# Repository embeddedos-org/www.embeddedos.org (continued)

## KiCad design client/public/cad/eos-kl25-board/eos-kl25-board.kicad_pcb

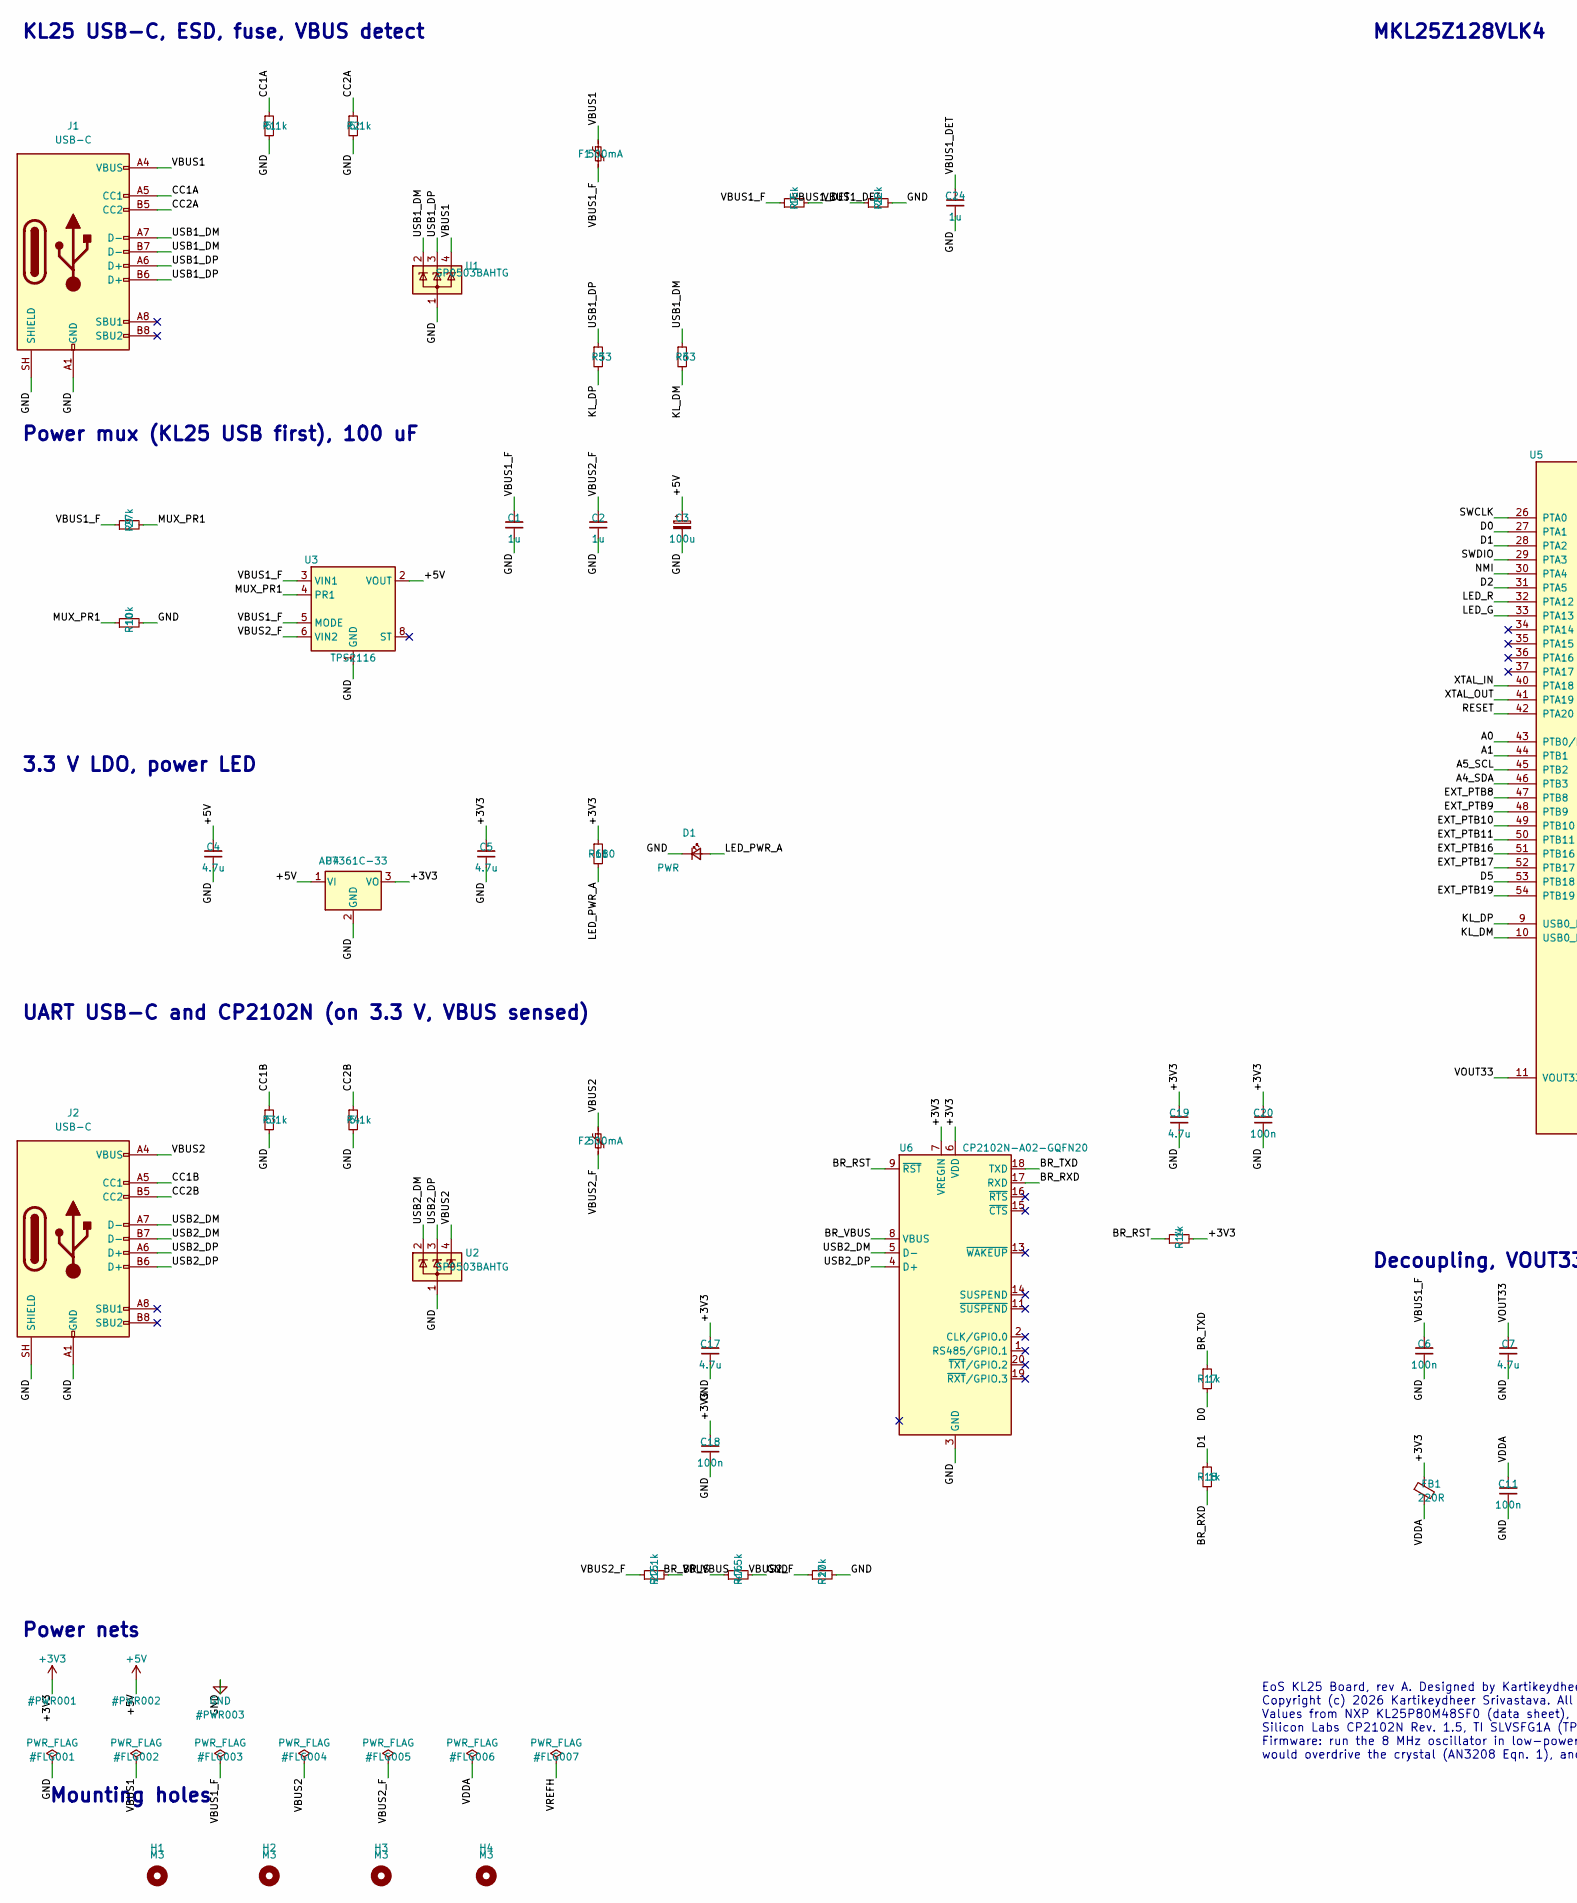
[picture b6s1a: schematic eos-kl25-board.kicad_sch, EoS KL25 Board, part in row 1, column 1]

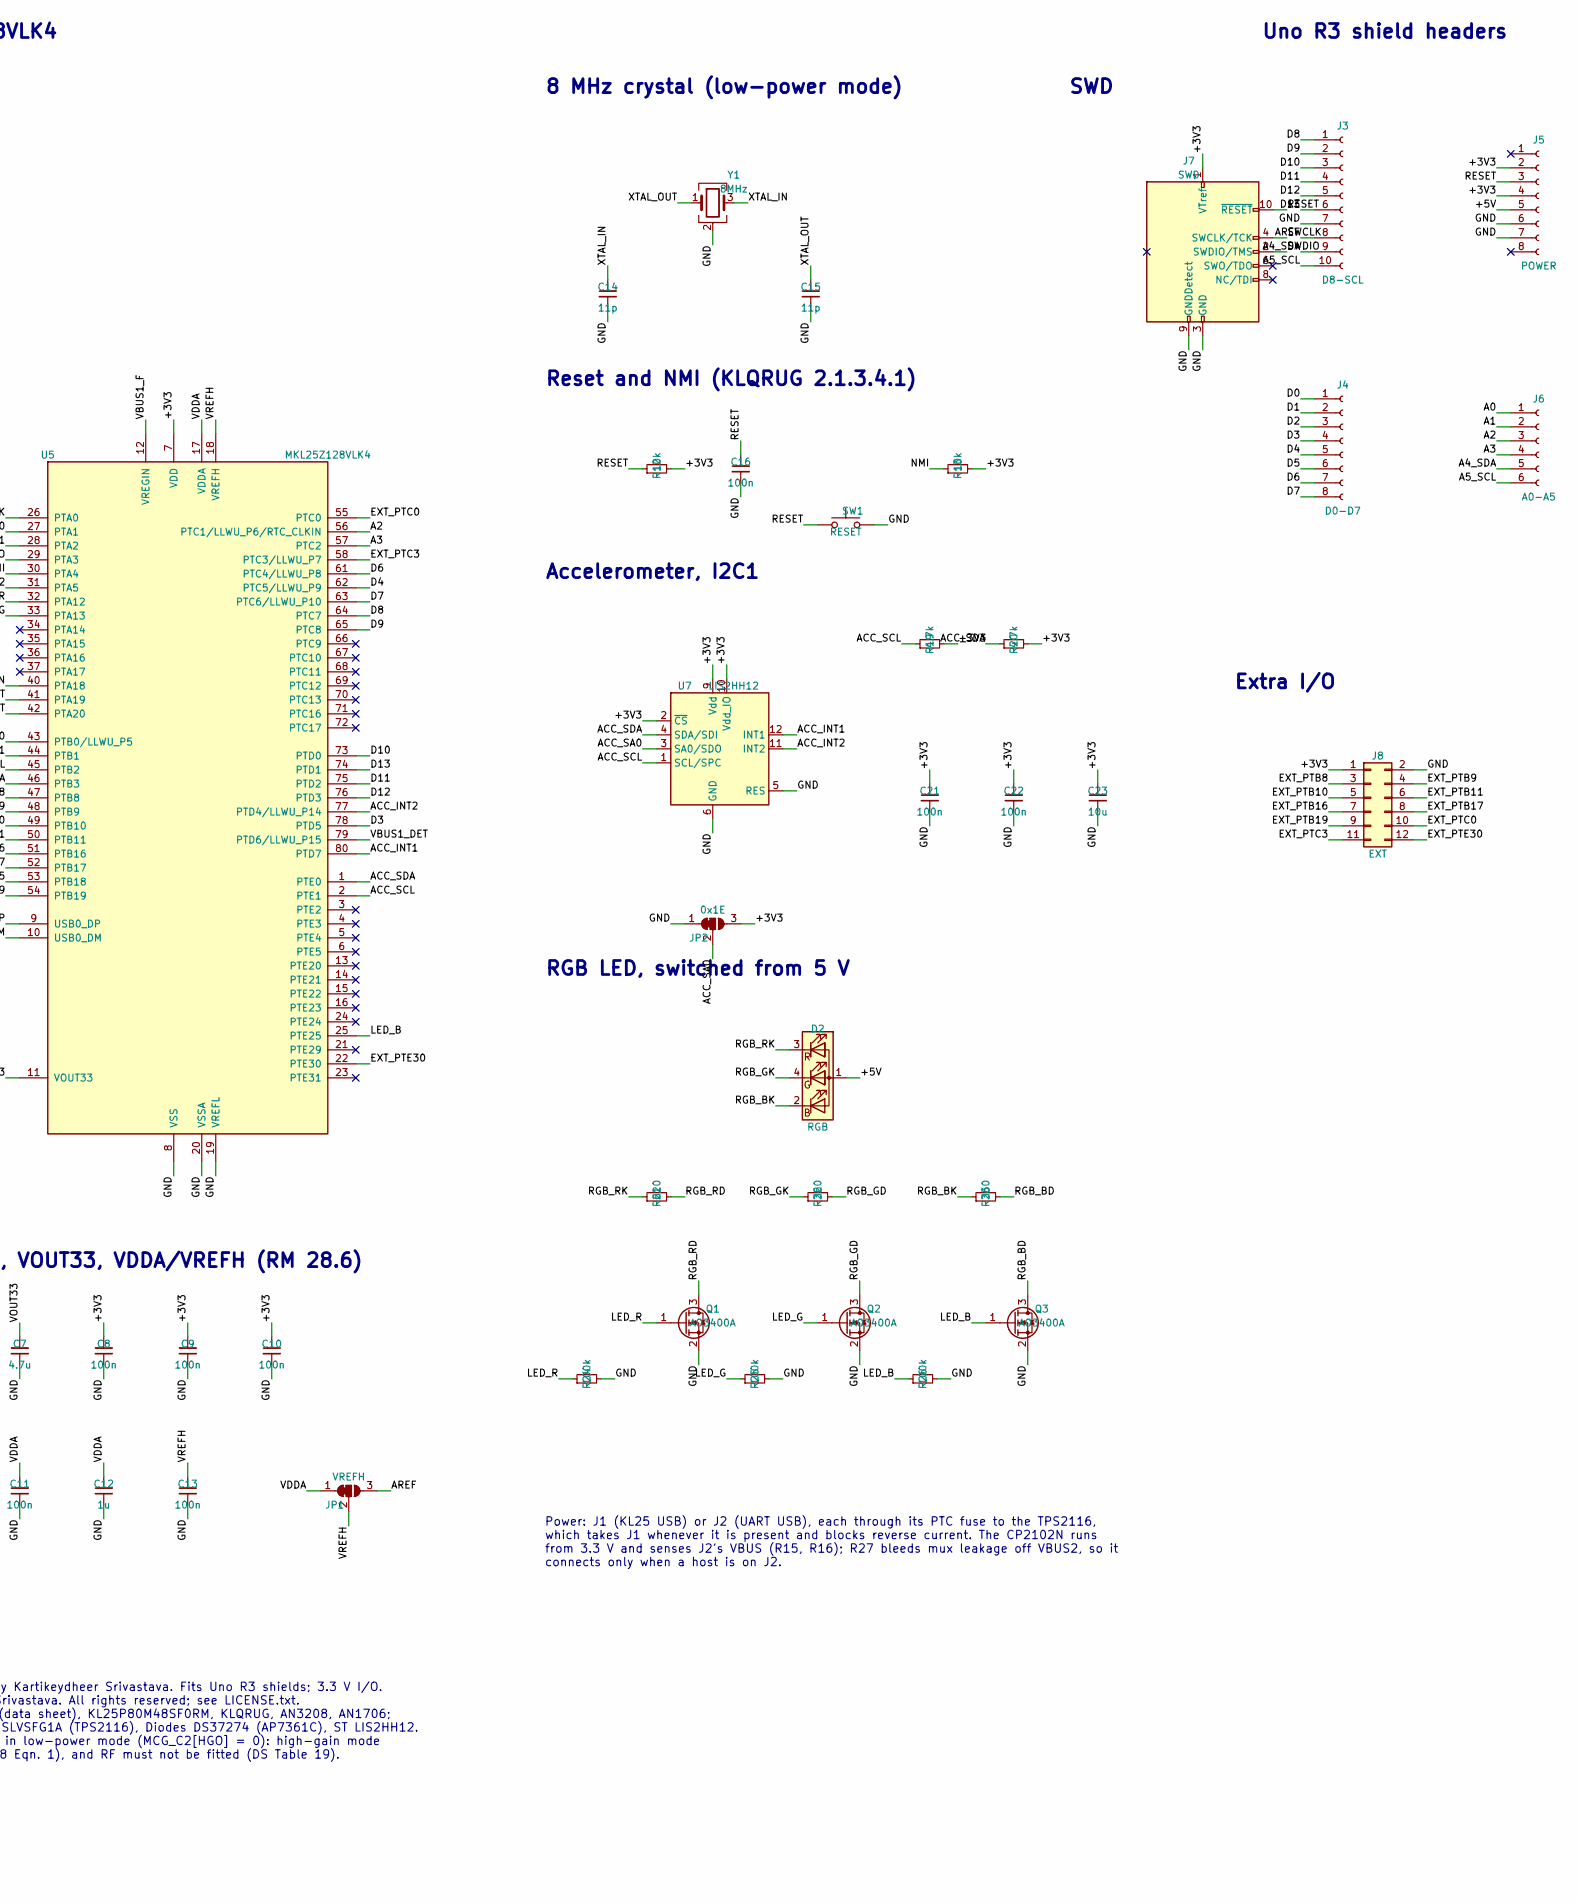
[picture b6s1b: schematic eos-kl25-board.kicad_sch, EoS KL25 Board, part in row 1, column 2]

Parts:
C1, C2, C12, C24: 1u; C_0603_1608Metric; MPN GCM188R71C105KA64D
C3: 100u; CP_Elec_6.3x5.8; MPN EEE-FK1C101P
C4: 4.7u; C_0805_2012Metric; MPN GRM219R61E475KA73D
C5, C7, C17, C19: 4.7u; C_0805_2012Metric; MPN GRM21BR71A475KE51L
C6, C8, C9, C10, C11, C13, C16, C18, C20, C21, C22: 100n; C_0402_1005Metric; MPN GRM155R71C104KA88D
C14, C15: 11p; C_0402_1005Metric; MPN GJM1555C1H110JB01D
C23: 10u; C_0805_2012Metric; MPN GRM21BR61C106KE15L
D1: PWR; LED_0603_1608Metric; MPN APTD1608LCGCK
D2: RGB; LED_RGB_Wuerth-PLCC4_3.2x2.8mm_150141M173100; MPN 150141M173100
F1, F2: 500mA; Fuse_1206_3216Metric; MPN MF-NSMF050/8X-2
FB1: 220R; L_0603_1608Metric; MPN BLM18PG221SN1D
H1, H2, H3, H4: M3; MountingHole_3.2mm_M3_ISO14580
J1, J2: USB-C; USB_C_Receptacle_HRO_TYPE-C-31-M-12; MPN TYPE-C-31-M-12
J3: D8-SCL; PinSocket_1x10_P2.54mm_Vertical; MPN SSW-110-01-T-S
J4: D0-D7; PinSocket_1x08_P2.54mm_Vertical; MPN SSW-108-01-T-S
J5: POWER; PinSocket_1x08_P2.54mm_Vertical; MPN SSW-108-01-T-S
J6: A0-A5; PinSocket_1x06_P2.54mm_Vertical; MPN SSW-106-01-T-S
J7: SWD; PinHeader_2x05_P1.27mm_Vertical_SMD; MPN FTSH-105-01-L-DV-K
J8: EXT; PinHeader_2x06_P2.54mm_Vertical; MPN TSW-106-07-G-D
JP1: VREFH; SolderJumper-3_P1.3mm_Bridged12_RoundedPad1.0x1.5mm
JP2: 0x1E; SolderJumper-3_P1.3mm_Bridged12_RoundedPad1.0x1.5mm
Q1, Q2, Q3: AO3400A; SOT-23; MPN AO3400A
R1, R2, R3, R4: 5.1k; R_0402_1005Metric; MPN RC0402FR-075K1L
R5, R6: 33; R_0402_1005Metric; MPN RC0402FR-0733RL
R7: 15k; R_0402_1005Metric; MPN RC0402FR-0715KL
R8: 22k; R_0402_1005Metric; MPN RC0402FR-0722KL
R9: 27k; R_0402_1005Metric; MPN RC0402FR-0727KL
R10, R12, R13, R27: 10k; R_0402_1005Metric; MPN RC0402FR-0710KL
R11: 680; R_0402_1005Metric; MPN RC0402FR-07680RL
R14, R17, R18: 1k; R_0402_1005Metric; MPN RC0402FR-071KL
R15: 22.1k; R_0402_1005Metric; MPN RC0402FR-0722K1L
R16: 47.5k; R_0402_1005Metric; MPN RC0402FR-0747K5L
R19, R20: 4.7k; R_0402_1005Metric; MPN RC0402FR-074K7L
R21: 620; R_0402_1005Metric; MPN RC0402FR-07620RL
R22, R23: 360; R_0402_1005Metric; MPN RC0402FR-07360RL
R24, R25, R26: 100k; R_0402_1005Metric; MPN RC0402FR-07100KL
SW1: RESET; SW_Push_1P1T_NO_CK_KMR2; MPN KMR221G LFS
U1, U2: SP0503BAHTG; SOT-143; MPN SP0503BAHTG
U3: TPS2116; SOT-583-8; MPN TPS2116DRLR
U4: AP7361C-33; SOT-223-3_TabPin2; MPN AP7361C-33E-13
U5: MKL25Z128VLK4; LQFP-80_12x12mm_P0.5mm; MPN MKL25Z128VLK4
U6: CP2102N-A02-GQFN20; SiliconLabs_QFN-20-1EP_3x3mm_P0.5mm_EP1.8x1.8mm; MPN CP2102N-A02-GQFN20
U7: LIS2HH12; LGA-12_2x2mm_P0.5mm; MPN LIS2HH12TR
Y1: 8MHz; Crystal_SMD_5032-4Pin_5.0x3.2mm; MPN ECS-80-10-30B-CWN-TR

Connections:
+3V3: C5.1, C8.1, C9.1, C10.1, C17.1, C18.1, C19.1, C20.1, C21.1, C22.1, C23.1, FB1.1, J5.2, J5.4, J7.1 (VTref), J8.1, JP2.3 (B), R11.1, R12.2, R13.2, R14.2, R19.2, R20.2, U4.3 (VO), U5.7 (VDD), U5.38 (VDD), U5.60 (VDD), U6.6 (VDD), U6.7 (VREGIN), U7.2 (~CS), U7.9 (Vdd), U7.10 (Vdd_IO)
+5V: C3.1, C4.1, D2.1 (A), J5.5, U3.2 (VOUT), U3.7 (VOUT), U4.1 (VI)
/A0: J6.1, U5.43 (PTB0/LLWU_P5)
/A1: J6.2, U5.44 (PTB1)
/A2: J6.3, U5.56 (PTC1/LLWU_P6/RTC_CLKIN)
/A3: J6.4, U5.57 (PTC2)
/A4_SDA: J3.9, J6.5, U5.46 (PTB3)
/A5_SCL: J3.10, J6.6, U5.45 (PTB2)
/ACC_INT1: U5.80 (PTD7), U7.12 (INT1)
/ACC_INT2: U5.77 (PTD4/LLWU_P14), U7.11 (INT2)
/ACC_SA0: JP2.2 (C), U7.3 (SA0/SDO)
/ACC_SCL: R19.1, U5.2 (PTE1), U7.1 (SCL/SPC)
/ACC_SDA: R20.1, U5.1 (PTE0), U7.4 (SDA/SDI)
/AREF: J3.8, JP1.3 (B)
/BR_RST: R14.1, U6.9 (~RST)
/BR_RXD: R18.2, U6.17 (RXD)
/BR_TXD: R17.1, U6.18 (TXD)
/BR_VBUS: R15.2, R16.1, U6.8 (VBUS)
/CC1A: J1.A5 (CC1), R1.1
/CC1B: J2.A5 (CC1), R3.1
/CC2A: J1.B5 (CC2), R2.1
/CC2B: J2.B5 (CC2), R4.1
/D0: J4.1, R17.2, U5.27 (PTA1)
/D1: J4.2, R18.1, U5.28 (PTA2)
/D2: J4.3, U5.31 (PTA5)
/D3: J4.4, U5.78 (PTD5)
/D4: J4.5, U5.62 (PTC5/LLWU_P9)
/D5: J4.6, U5.53 (PTB18)
/D6: J4.7, U5.61 (PTC4/LLWU_P8)
/D7: J4.8, U5.63 (PTC6/LLWU_P10)
/D8: J3.1, U5.64 (PTC7)
/D9: J3.2, U5.65 (PTC8)
/D10: J3.3, U5.73 (PTD0)
/D11: J3.4, U5.75 (PTD2)
/D12: J3.5, U5.76 (PTD3)
/D13: J3.6, U5.74 (PTD1)
/EXT_PTB8: J8.3, U5.47 (PTB8)
/EXT_PTB9: J8.4, U5.48 (PTB9)
/EXT_PTB10: J8.5, U5.49 (PTB10)
/EXT_PTB11: J8.6, U5.50 (PTB11)
/EXT_PTB16: J8.7, U5.51 (PTB16)
/EXT_PTB17: J8.8, U5.52 (PTB17)
/EXT_PTB19: J8.9, U5.54 (PTB19)
/EXT_PTC0: J8.10, U5.55 (PTC0)
/EXT_PTC3: J8.11, U5.58 (PTC3/LLWU_P7)
/EXT_PTE30: J8.12, U5.22 (PTE30)
/KL_DM: R6.2, U5.10 (USB0_DM)
/KL_DP: R5.2, U5.9 (USB0_DP)
/LED_B: Q3.1 (G), R26.1, U5.25 (PTE25)
/LED_G: Q2.1 (G), R25.1, U5.33 (PTA13)
/LED_PWR_A: D1.2 (A), R11.2
/LED_R: Q1.1 (G), R24.1, U5.32 (PTA12)
/MUX_PR1: R9.2, R10.1, U3.4 (PR1)
/NMI: R13.1, U5.30 (PTA4)
/RESET: C16.1, J5.3, J7.10 (~RESET), R12.1, SW1.1, U5.42 (PTA20)
/RGB_BD: Q3.3 (D), R23.2
/RGB_BK: D2.2 (BK), R23.1
/RGB_GD: Q2.3 (D), R22.2
/RGB_GK: D2.4 (GK), R22.1
/RGB_RD: Q1.3 (D), R21.2
/RGB_RK: D2.3 (RK), R21.1
/SWCLK: J7.4 (SWCLK/TCK), U5.26 (PTA0)
/SWDIO: J7.2 (SWDIO/TMS), U5.29 (PTA3)
/USB1_DM: J1.A7 (D-), J1.B7 (D-), R6.1, U1.2 (K)
/USB1_DP: J1.A6 (D+), J1.B6 (D+), R5.1, U1.3 (K)
/USB2_DM: J2.A7 (D-), J2.B7 (D-), U2.2 (K), U6.5 (D-)
/USB2_DP: J2.A6 (D+), J2.B6 (D+), U2.3 (K), U6.4 (D+)
/VBUS1: F1.1, J1.A4 (VBUS), J1.A9 (VBUS), J1.B4 (VBUS), J1.B9 (VBUS), U1.4 (K)
/VBUS1_DET: C24.1, R7.2, R8.1, U5.79 (PTD6/LLWU_P15)
/VBUS1_F: C1.1, C6.1, F1.2, R7.1, R9.1, U3.3 (VIN1), U3.5 (MODE), U5.12 (VREGIN)
/VBUS2: F2.1, J2.A4 (VBUS), J2.A9 (VBUS), J2.B4 (VBUS), J2.B9 (VBUS), U2.4 (K)
/VBUS2_F: C2.1, F2.2, R15.1, R27.1, U3.6 (VIN2)
/VDDA: C11.1, C12.1, FB1.2, JP1.1 (A), U5.17 (VDDA)
/VOUT33: C7.1, U5.11 (VOUT33)
/VREFH: C13.1, JP1.2 (C), U5.18 (VREFH)
/XTAL_IN: C14.1, U5.40 (PTA18), Y1.3
/XTAL_OUT: C15.1, U5.41 (PTA19), Y1.1
GND: C1.2, C2.2, C3.2, C4.2, C5.2, C6.2, C7.2, C8.2, C9.2, C10.2, C11.2, C12.2, C13.2, C14.2, C15.2, C16.2, C17.2, C18.2, C19.2, C20.2, C21.2, C22.2, C23.2, C24.2, D1.1 (K), J1.A1 (GND), J1.A12 (GND), J1.B1 (GND), J1.B12 (GND), J1.SH (SHIELD), J2.A1 (GND), J2.A12 (GND), J2.B1 (GND), J2.B12 (GND), J2.SH (SHIELD), J3.7, J5.6, J5.7, J7.3 (GND), J7.5 (GND), J7.9 (GNDDetect), J8.2, JP2.1 (A), Q1.2 (S), Q2.2 (S), Q3.2 (S), R1.2, R2.2, R3.2, R4.2, R8.2, R10.2, R16.2, R24.2, R25.2, R26.2, R27.2, SW1.2, U1.1 (A), U2.1 (A), U3.1 (GND), U4.2 (GND), U5.8 (VSS), U5.19 (VREFL), U5.20 (VSSA), U5.39 (VSS), U5.59 (VSS), U6.3 (GND), U6.12 (GND), U6.21 (GND), U7.5 (RES), U7.6 (GND), U7.7 (GND), U7.8 (GND), Y1.2 (G), Y1.4 (G)

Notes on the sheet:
KL25 USB-C, ESD, fuse, VBUS detect
Power mux (KL25 USB first), 100 uF
3.3 V LDO, power LED
UART USB-C and CP2102N (on 3.3 V, VBUS sensed)
MKL25Z128VLK4
Decoupling, VOUT33, VDDA/VREFH (RM 28.6)
8 MHz crystal (low-power mode)
Reset and NMI (KLQRUG 2.1.3.4.1)
SWD
Accelerometer, I2C1
RGB LED, switched from 5 V
Uno R3 shield headers
Extra I/O
Mounting holes
Power nets
EoS KL25 Board, rev A. Designed by Kartikeydheer Srivastava. Fits Uno R3 shields; 3.3 V I/O. Copyright (c) 2026 Kartikeydheer Srivastava. All rights reserved; see LICENSE.txt. Values from NXP KL25P80M48SF0 (data sheet), KL25P80M48SF0RM, KLQRUG, AN3208, AN1706; Silicon Labs CP2102N Rev. 1.5, TI SLVS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
Power: J1 (KL25 USB) or J2 (UART USB), each through its PTC fuse to the TPS2116, which takes J1 whenever it is present and blocks reverse current. The CP2102N runs from 3.3 V and senses J2's VBUS (R15, R16); R27 bleeds mux leakage off VBUS2, so it connects only when a host is on J2.

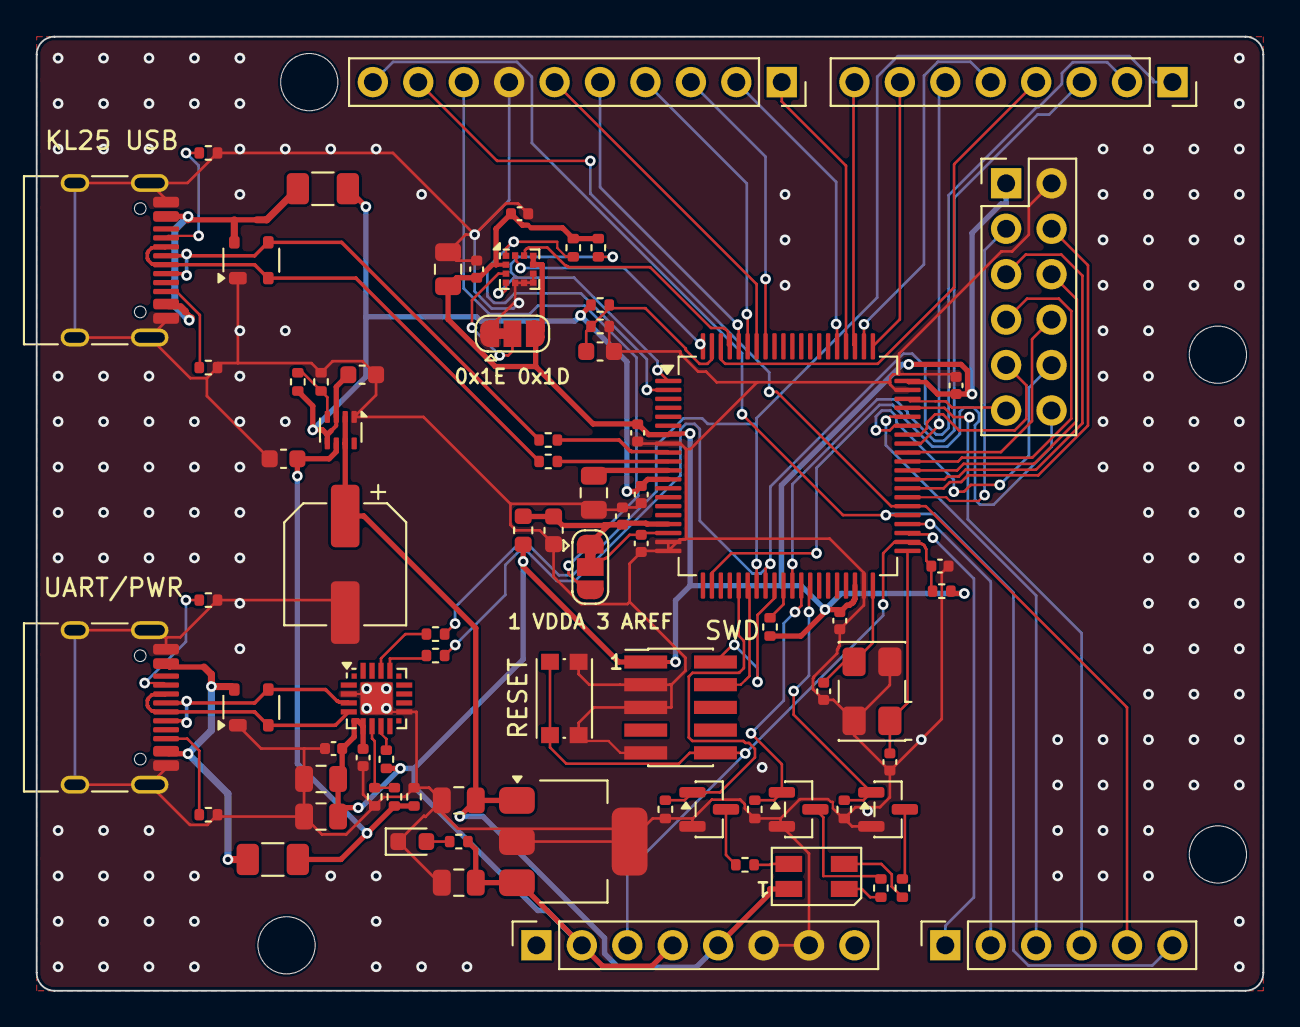
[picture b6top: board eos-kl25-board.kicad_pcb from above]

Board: 2 copper layers, 68.6 x 53.3 mm, 82 parts (1 on the bottom side), 78 nets.
